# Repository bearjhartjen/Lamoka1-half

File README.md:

<h1 align="center">
  
  <br>
  Lamoka1/2
</h1>

<p align="center">
  PIE v1.9 works on this board.
  For more information on PIE, go
  <a href="SOFTWARE/README.md">here</a>.
</p>

<p align="center">
  <a href="https://htmlpreview.github.io/?https://raw.githubusercontent.com/bearjhartjen/Lamoka1-half/master/HARDWARE/Kicadfiles/Lamoka1-half/BOM/ibom.html">
    <strong>View Interactive BOM</strong>
  </a>
</p>

---

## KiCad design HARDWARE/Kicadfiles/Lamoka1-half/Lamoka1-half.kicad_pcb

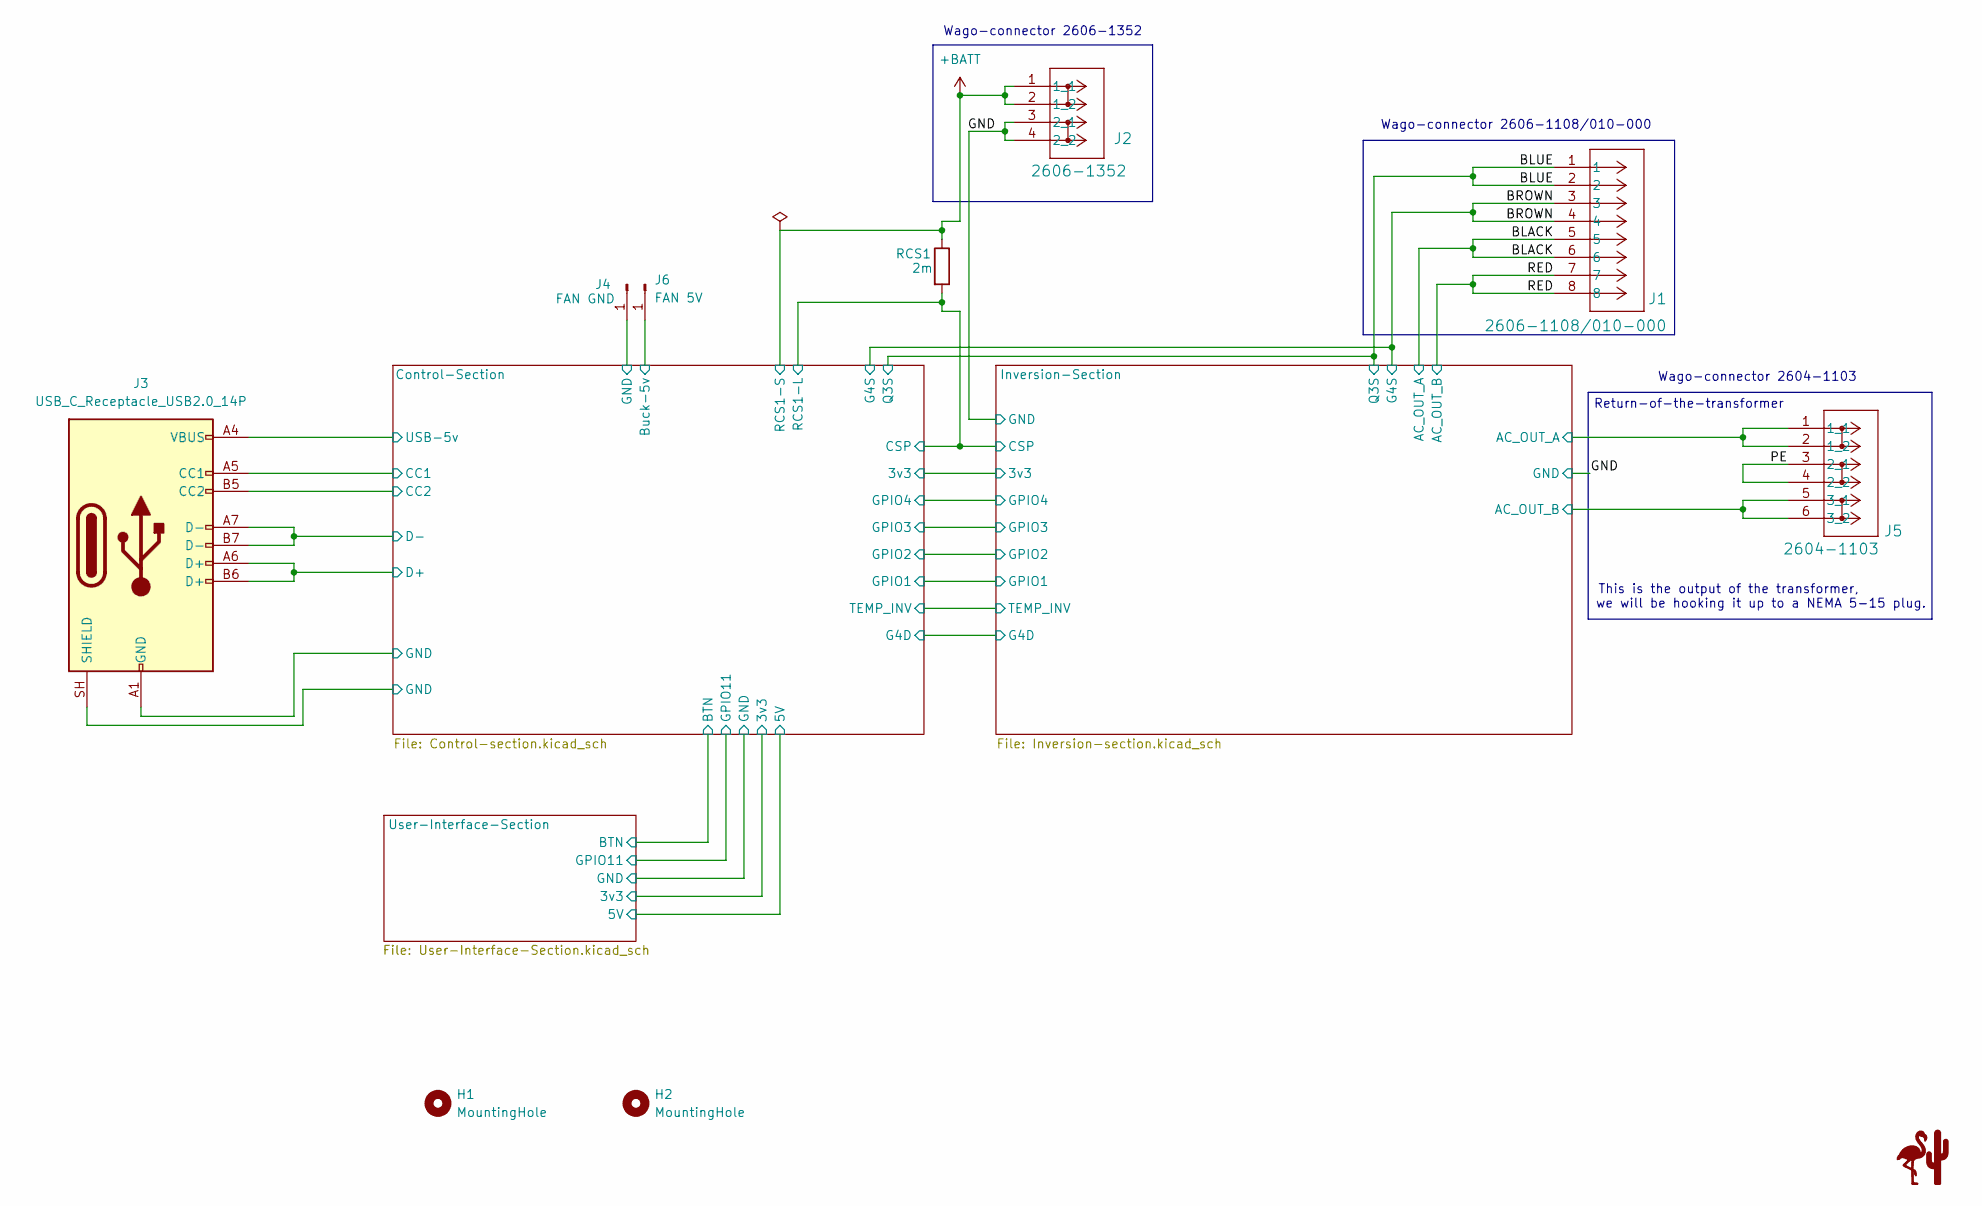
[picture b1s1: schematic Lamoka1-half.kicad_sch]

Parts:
H1, H2: MountingHole; MountingHole_3.2mm_M3
J1: 2606-1108/010-000; CONN8_2606-1108&slash_010-000_WAG; MPN 2606-1108/010-000
J2: 2606-1352; CONN2_2606-1352_WAG; MPN 2606-1352
J3: USB_C_Receptacle_USB2.0_14P; USB_C_Receptacle_HRO_TYPE-C-31-M-12; MPN TYPE-C-31-M-12
J4: FAN GND; SolderWirePad_1x01_SMD_3x6mm
J5: 2604-1103; CONN3_2604-1103_WAG; MPN 2604-1103
J6: FAN 5V; SolderWirePad_1x01_SMD_3x6mm
RCS1: 2m; R_2512_6332Metric; MPN CSNL2512FT2L00

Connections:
+BATT: J2.1 (1_1), J2.2 (1_2), RCS1.1; also elsewhere on the board
/BLACK: J1.5, J1.6, J5.1 (1_1), J5.2 (1_2)
/BLUE: J1.1, J1.2; also elsewhere on the board
/BROWN: J1.3, J1.4; also elsewhere on the board
/Control-Section/Buck-5v: J6.1 (Pin_1_1); also elsewhere on the board
/Control-Section/CC1: J3.A5 (CC1); also elsewhere on the board
/Control-Section/CC2: J3.B5 (CC2); also elsewhere on the board
/Control-Section/D+: J3.A6 (D+), J3.B6 (D+); also elsewhere on the board
/Control-Section/D-: J3.A7 (D-), J3.B7 (D-); also elsewhere on the board
/Control-Section/USB-5v: J3.A4 (VBUS), J3.A9 (VBUS), J3.B4 (VBUS), J3.B9 (VBUS); also elsewhere on the board
/Inversion-Section/CSP: RCS1.2; also elsewhere on the board
/PE: J5.3 (2_1), J5.4 (2_2)
/RED: J1.7, J1.8, J5.5 (3_1), J5.6 (3_2)
GND: J2.3 (2_1), J2.4 (2_2), J3.A1 (GND), J3.A12 (GND), J3.B1 (GND), J3.B12 (GND), J3.SH (SHIELD), J4.1 (Pin_1_1); also elsewhere on the board

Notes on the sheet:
This is the output of the transformer,
Wago-connector 2606-1108/010-000
Wago-connector 2604-1103
Return-of-the-transformer
Wago-connector 2606-1352
we will be hooking it up to a NEMA 5-15 plug.

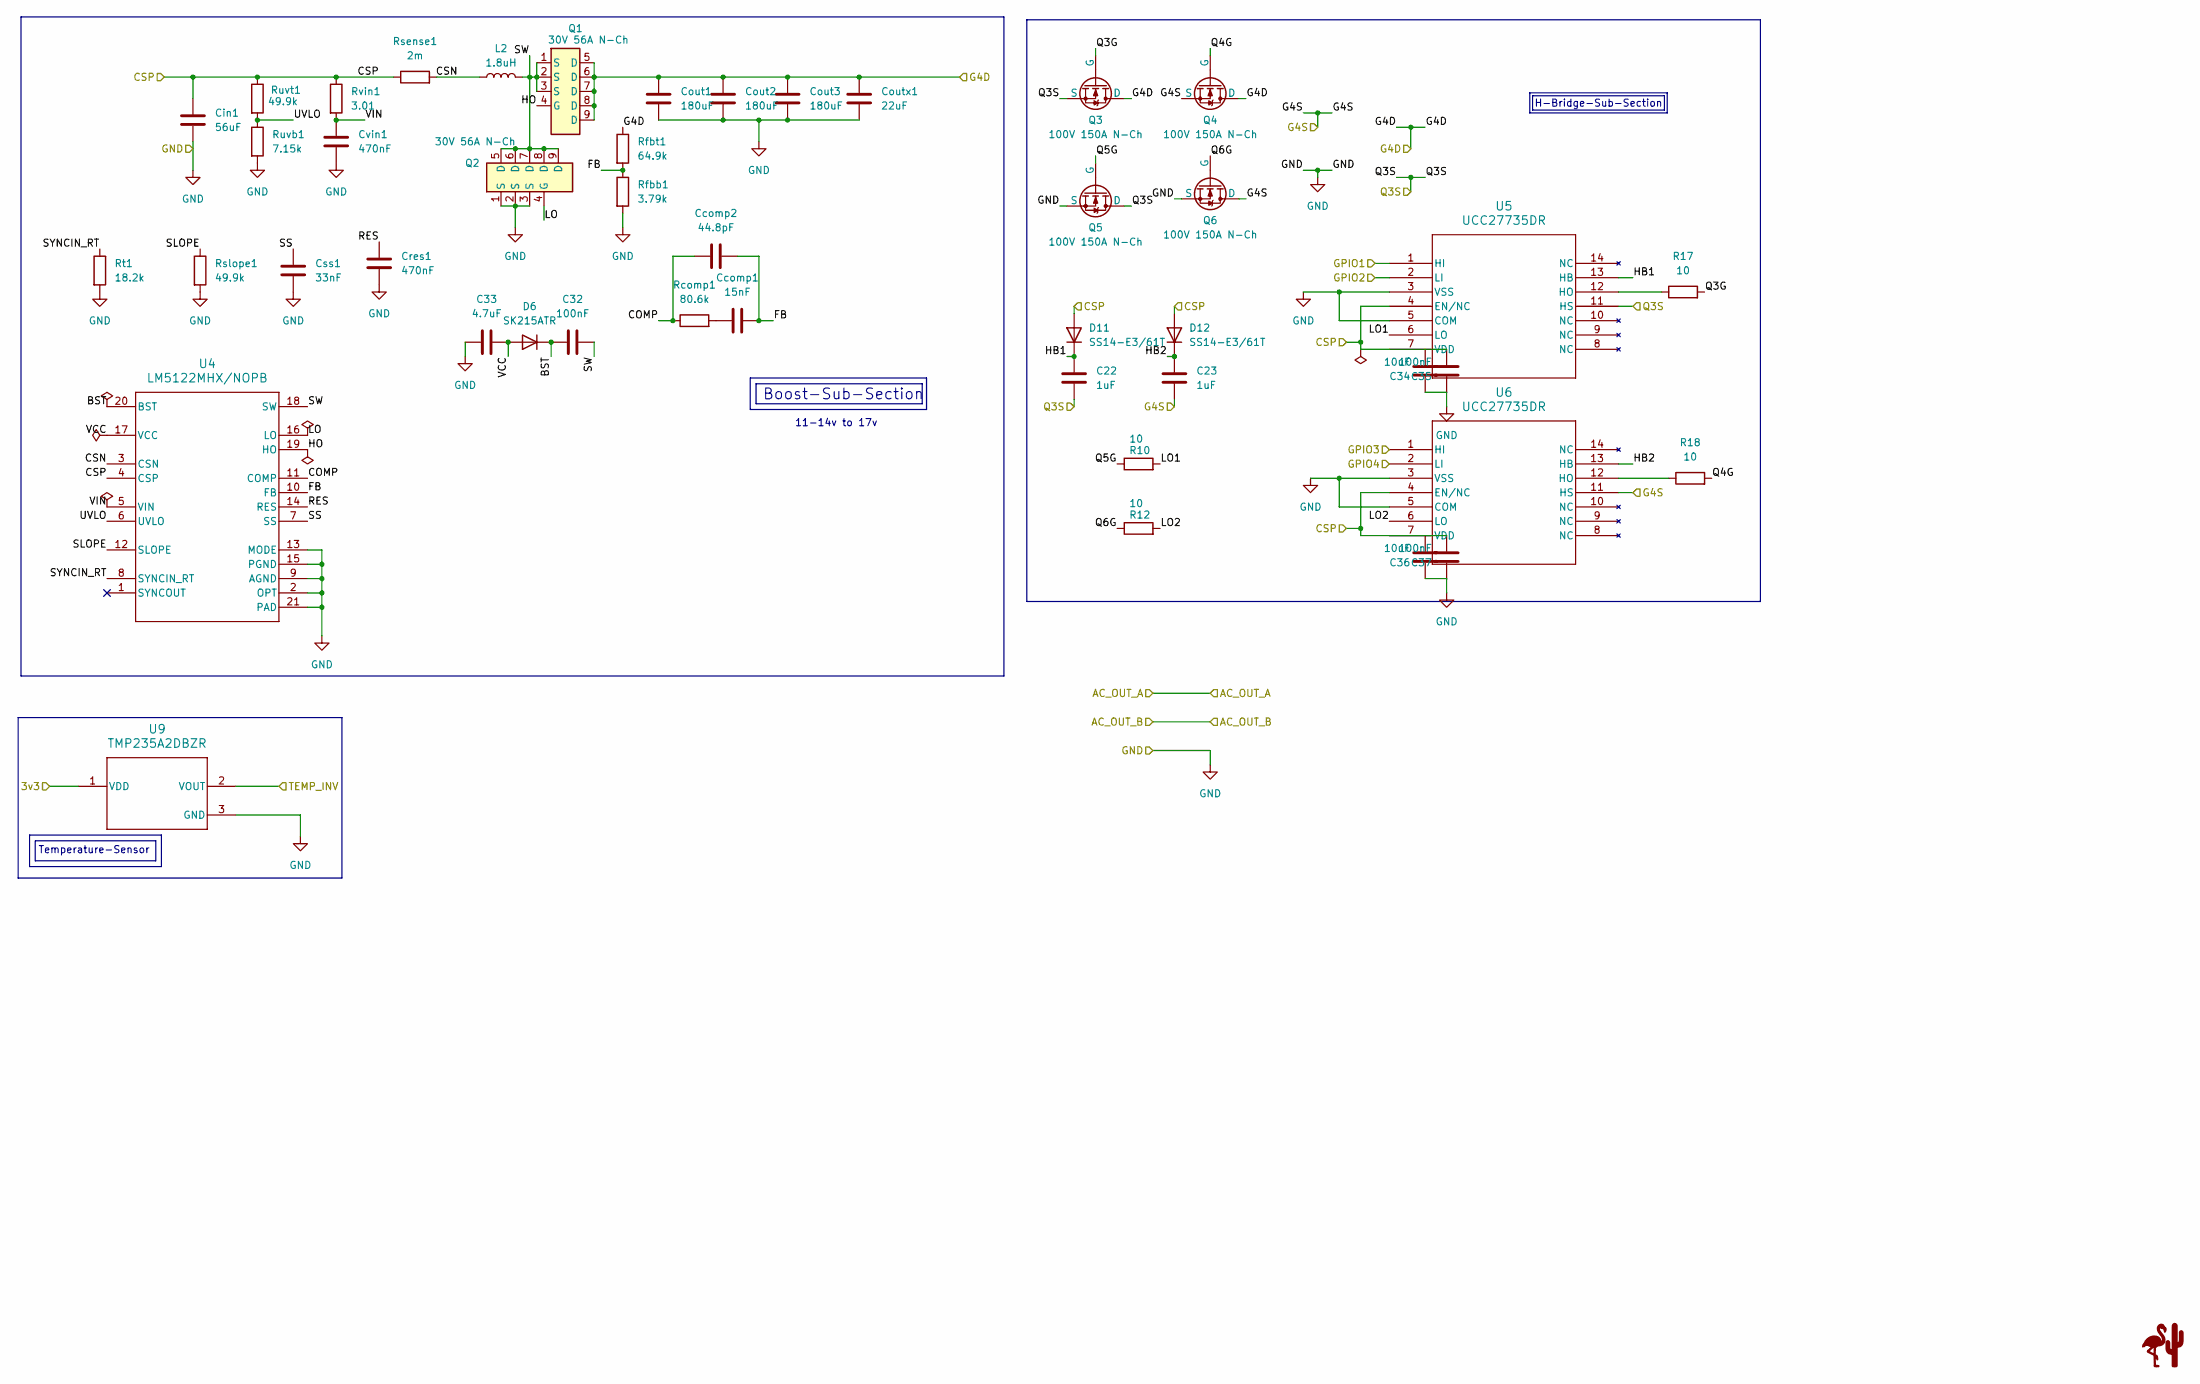
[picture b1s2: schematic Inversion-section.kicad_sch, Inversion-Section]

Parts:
C22, C23: 1uF; C_0805_2012Metric; MPN GRM21BR71H105KA12L
C32: 100nF; C_0805_2012Metric; MPN 08053C104KAT2A
C33: 4.7uF; C_0805_2012Metric; MPN MSAST21GAB5475MTNAO1
C34, C36: 10uF; C_0805_2012Metric; MPN GRM21BZ71E106KE15L
C35, C37: 100nF; C_0603_1608Metric; MPN CL10B104KB8NNNC
Ccomp1: 15nF; C_0805_2012Metric; MPN CGA4F1C0G2A153J085AE
Ccomp2: 44.8pF; C_0402_1005Metric; MPN GRM1555C1H448JA01D
Cin1: 56uF; CP_Elec_5x5.9; MPN 20SVPF56MX
Cout1: 180uF; CP_Elec_8x11.9_Cout1; MPN 35SVPK180M
Cout2: 180uF; CP_Elec_8x11.9_Cout2; MPN 35SVPK180M
Cout3: 180uF; CP_Elec_8x11.9_Cout3; MPN 35SVPK180M
Coutx1: 22uF; C_1206_3216Metric; MPN C3216X5R1V226M160AC
Cres1: 470nF; C_0805_2012Metric; MPN TMK212BJ474KD-T
Css1: 33nF; C_0402_1005Metric; MPN GRM155R71A333KA01D
Cvin1: 470nF; C_0402_1005Metric; MPN C1005X5R1V474K050BC
D6: SK215ATR; D_SMA; MPN SK215ATR
D11, D12: SS14-E3/61T; D_SMA; MPN SS14-E3/61T
L2: 1.8uH; L_Coilcraft_XAL1580-182; MPN XAL1580-182MEB
Q1, Q2: 30V 56A N-Ch; DQG0008A; MPN CSD17304Q3
Q3, Q4, Q5, Q6: 100V 150A N-Ch; TO-220-3_Vertical; MPN CSD19536KCS
R10, R12, R17, R18: 10; R_1206_3216Metric; MPN RC1206FR-0710RL
Rcomp1: 80.6k; R_0201_0603Metric; MPN RC0201FR-0780K6L
Rfbb1: 3.79k; R_0402_1005Metric; MPN CRCW04023K79FKED
Rfbt1: 64.9k; R_0402_1005Metric; MPN CRCW040264K9FKED
Rsense1: 2m; R_2512_6332Metric; MPN CSNL2512FT2L00
Rslope1: 49.9k; R_0201_0603Metric; MPN RC0201FR-0749K9L
Rt1: 18.2k; R_0402_1005Metric; MPN CRCW040218K2FKED
Ruvb1: 7.15k; R_0402_1005Metric; MPN CRCW04027K15FKED
Ruvt1: 49.9k; R_0402_1005Metric; MPN CRCW040249K9FKED
Rvin1: 3.01; R_0402_1005Metric; MPN CRCW04023R01FKED
U4: LM5122MHX/NOPB; PWP0020A_N; MPN LM5122MHX/NOPB
U5, U6: UCC27735DR; SOIC_14L_TEX; MPN UCC27735DR
U9: TMP235A2DBZR; DBZ0003A-IPC_A; MPN TMP235A2DBZR

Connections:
/BLUE: C22.2, Q3.3 (S), Q5.2 (D), U5.11 (HS); also elsewhere on the board
/BROWN: C23.2, Q4.3 (S), Q6.2 (D), U6.11 (HS); also elsewhere on the board
/Control-Section/3v3: U9.1 (VDD); also elsewhere on the board
/Control-Section/GPIO1: U5.1 (HI); also elsewhere on the board
/Control-Section/GPIO2: U5.2 (LI); also elsewhere on the board
/Control-Section/GPIO3: U6.1 (HI); also elsewhere on the board
/Control-Section/GPIO4: U6.2 (LI); also elsewhere on the board
/Control-Section/TEMP_INV: U9.2 (VOUT); also elsewhere on the board
/Inversion-Section/BST: C32.1, D6.1 (K), U4.20 (BST)
/Inversion-Section/COMP: Ccomp2.1, Rcomp1.1, U4.11 (COMP)
/Inversion-Section/CSN: L2.1, Rsense1.2, U4.3 (CSN)
/Inversion-Section/CSP: C34.2, C35.2, C36.2, C37.2, Cin1.1, D11.2 (A), D12.2 (A), Rsense1.1, Ruvt1.1, Rvin1.1, U4.4 (CSP), U5.4 (EN/NC), U5.7 (VDD), U6.4 (EN/NC), U6.7 (VDD); also elsewhere on the board
/Inversion-Section/FB: Ccomp1.2, Ccomp2.2, Rfbb1.1, Rfbt1.2, U4.10 (FB)
/Inversion-Section/G4D: Cout1.1, Cout2.1, Cout3.1, Coutx1.1, Q1.5 (D), Q1.6 (D), Q1.7 (D), Q1.8 (D), Q1.9 (D), Q3.2 (D), Q4.2 (D), Rfbt1.1; also elsewhere on the board
/Inversion-Section/HB1: C22.1, D11.1 (K), U5.13 (HB)
/Inversion-Section/HB2: C23.1, D12.1 (K), U6.13 (HB)
/Inversion-Section/HO: Q1.4 (G), U4.19 (HO)
/Inversion-Section/LO: Q2.4 (G), U4.16 (LO)
/Inversion-Section/LO1: R10.2, U5.6 (LO)
/Inversion-Section/LO2: R12.2, U6.6 (LO)
/Inversion-Section/Q3G: Q3.1 (G), R17.2
/Inversion-Section/Q4G: Q4.1 (G), R18.2
/Inversion-Section/Q5G: Q5.1 (G), R10.1
/Inversion-Section/Q6G: Q6.1 (G), R12.1
/Inversion-Section/RES: Cres1.1, U4.14 (RES)
/Inversion-Section/SLOPE: Rslope1.1, U4.12 (SLOPE)
/Inversion-Section/SS: Css1.1, U4.7 (SS)
/Inversion-Section/SW: C32.2, L2.2, Q1.1 (S), Q1.2 (S), Q1.3 (S), Q2.5 (D), Q2.6 (D), Q2.7 (D), Q2.8 (D), Q2.9 (D), U4.18 (SW)
/Inversion-Section/SYNCIN_RT: Rt1.1, U4.8 (SYNCIN_RT)
/Inversion-Section/UVLO: Ruvb1.1, Ruvt1.2, U4.6 (UVLO)
/Inversion-Section/VCC: C33.2, D6.2 (A), U4.17 (VCC)
/Inversion-Section/VIN: Cvin1.1, Rvin1.2, U4.5 (VIN)
GND: C33.1, C34.1, C35.1, C36.1, C37.1, Cin1.2, Cout1.2, Cout2.2, Cout3.2, Coutx1.2, Cres1.2, Css1.2, Cvin1.2, Q2.1 (S), Q2.2 (S), Q2.3 (S), Q5.3 (S), Q6.3 (S), Rfbb1.2, Rslope1.2, Rt1.2, Ruvb1.2, U4.2 (OPT), U4.9 (AGND), U4.13 (MODE), U4.15 (PGND), U4.21 (PAD), U4.V, U5.3 (VSS), U5.5 (COM), U6.3 (VSS), U6.5 (COM), U9.3 (GND); also elsewhere on the board
unnamed: Ccomp1.1, Rcomp1.2
unnamed: R17.1, U5.12 (HO)
unnamed: R18.1, U6.12 (HO)

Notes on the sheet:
11-14v to 17v
H-Bridge-Sub-Section
Boost-Sub-Section
Temperature-Sensor

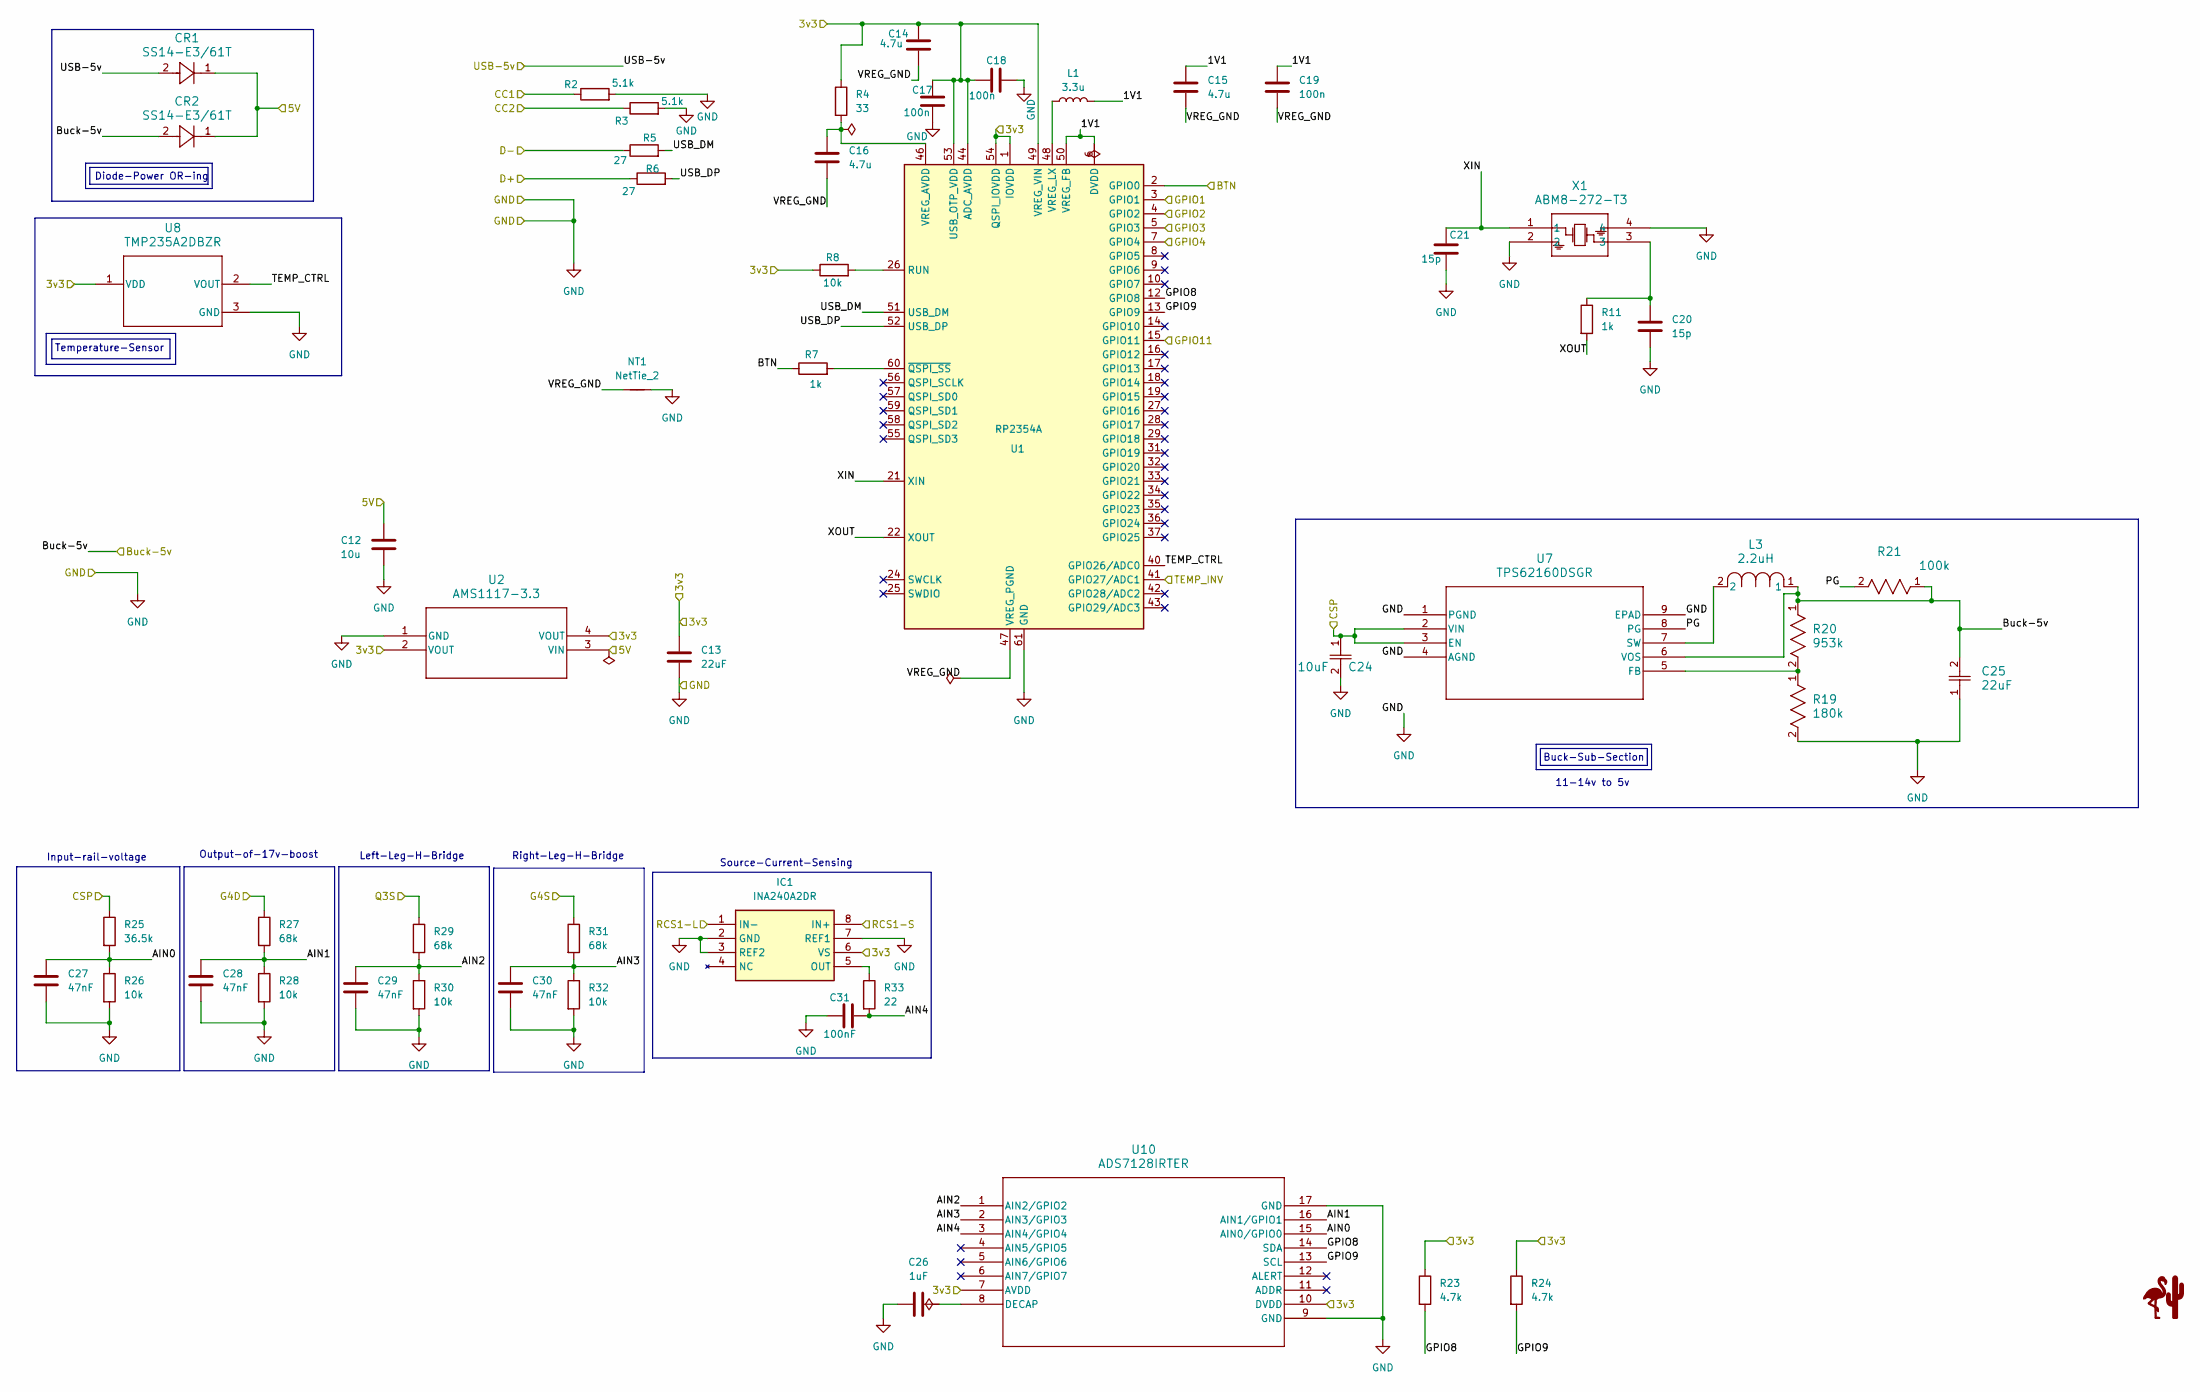
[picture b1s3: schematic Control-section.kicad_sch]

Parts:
C12: 10u; C_0402_1005Metric; MPN CL05A106MQ5NUNC
C13: 22uF; CP_EIA-3216-18_Kemet-A; MPN T491A226K010AT
C14, C15, C16: 4.7u; C_0603_1608Metric; MPN CL10A475KP8NNNC
C17, C18, C19: 100n; C_0402_1005Metric; MPN CL05B104KO5NNNC
C20, C21: 15p; C_0402_1005Metric; MPN 0402CG150J500NT
C24: 10uF; CAPC2114X145N; MPN TMK212BBJ106KG-T
C25: 22uF; G-31_MUR; MPN GRM31CR71A226KE15L
C26: 1uF; C_0603_1608Metric; MPN CL10A105KA8NNNC
C27, C28, C29, C30: 47nF; C_0603_1608Metric; MPN CL10B473KB8NNNC
C31: 100nF; C_0603_1608Metric; MPN CL10B104KB8NNNC
CR1, CR2: SS14-E3/61T; DO-214AC_VIS; MPN SS14-E3/61T
IC1: INA240A2DR; SOIC127P600X175-8N; MPN INA240A2DR; Mouser Part Number 595-INA240A2DR
L1: 3.3u; AOTAB201610S3R3101T; MPN AOTA-B201610S3R3-101-T
L3: 2.2uH; IND_PA4332.222NLT_PUL; MPN PA4332.222NLT
NT1: NetTie_2; NetTie-2_SMD_Pad0.5mm
R2, R3: 5.1k; RC0603N_YAG; MPN RC0603FR-075K1L
R4: 33; R_0603_1608Metric; MPN RC0603FR-0733RL
R5, R6: 27; R_0603_1608Metric; MPN RC0603FR-0727RL
R7, R11: 1k; R_0402_1005Metric; MPN RC0402FR-071KL
R8, R26, R28, R30, R32: 10k; R_0603_1608Metric; MPN RC0603FR-0710KL
R19: 180k; RC0603N_YAG; MPN RC0603FR-07180KL
R20: 953k; RC0402N_VIS; MPN CRCW0402953KFKED
R21: 100k; RES_CRCW_0402_VIS; MPN CRCW0402100KFKED
R23, R24: 4.7k; R_0603_1608Metric; MPN RC0603FR-074K7L
R25: 36.5k; R_0603_1608Metric; MPN RC0603FR-0736K5L
R27, R29, R31: 68k; R_0603_1608Metric; MPN RC0603FR-0768KL
R33: 22; R_0603_1608Metric; MPN RC0603FR-0722RL
U1: RP2354A; QFN-60-1EP_7x7mm_P0.4mm_EP3.4x3.4mm; MPN RP2354A
U2: AMS1117-3.3; SOT-223-3_TabPin2; MPN AMS1117-3.3
U7: TPS62160DSGR; DSG8_1P6X0P9; MPN TPS62160DSGR
U8: TMP235A2DBZR; DBZ0003A-IPC_A; MPN TMP235A2DBZR
U10: ADS7128IRTER; WQFN16_RTE_TEX; MPN ADS7128IRTER
X1: ABM8-272-T3; ABM8272T3; MPN ABM8-272-T3

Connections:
+BATT: IC1.8 (IN+); also elsewhere on the board
/BLUE: R29.1; also elsewhere on the board
/BROWN: R31.1; also elsewhere on the board
/Control-Section/1V1: C15.1, C19.1, L1.2, U1.6 (DVDD), U1.23 (DVDD), U1.39 (DVDD), U1.50 (VREG_FB)
/Control-Section/3v3: C13.1, C14.1, C17.1, C18.1, IC1.6 (VS), R4.1, R8.1, R23.1, R24.1, U1.1 (IOVDD), U1.11 (IOVDD), U1.20 (IOVDD), U1.30 (IOVDD), U1.38 (IOVDD), U1.44 (ADC_AVDD), U1.45 (IOVDD), U1.49 (VREG_VIN), U1.53 (USB_OTP_VDD), U1.54 (QSPI_IOVDD), U2.2 (VOUT), U2.4 (VOUT), U8.1 (VDD), U10.7 (AVDD), U10.10 (DVDD); also elsewhere on the board
/Control-Section/5V: C12.2, CR1.1, CR2.1, U2.3 (VIN); also elsewhere on the board
/Control-Section/AIN0: C27.1, R25.2, R26.1, U10.15 (AIN0/GPIO0)
/Control-Section/AIN1: C28.1, R27.2, R28.1, U10.16 (AIN1/GPIO1)
/Control-Section/AIN2: C29.1, R29.2, R30.1, U10.1 (AIN2/GPIO2)
/Control-Section/AIN3: C30.1, R31.2, R32.1, U10.2 (AIN3/GPIO3)
/Control-Section/AIN4: C31.1, R33.2, U10.3 (AIN4/GPIO4)
/Control-Section/BTN: R7.1, U1.2 (GPIO0); also elsewhere on the board
/Control-Section/Buck-5v: C25.2, CR2.2, L3.1, R20.1, R21.1, U7.6 (VOS); also elsewhere on the board
/Control-Section/CC1: R2.1; also elsewhere on the board
/Control-Section/CC2: R3.1; also elsewhere on the board
/Control-Section/D+: R6.1; also elsewhere on the board
/Control-Section/D-: R5.1; also elsewhere on the board
/Control-Section/GPIO1: U1.3 (GPIO1); also elsewhere on the board
/Control-Section/GPIO2: U1.4 (GPIO2); also elsewhere on the board
/Control-Section/GPIO3: U1.5 (GPIO3); also elsewhere on the board
/Control-Section/GPIO4: U1.7 (GPIO4); also elsewhere on the board
/Control-Section/GPIO8: R23.2, U1.12 (GPIO8), U10.14 (SDA)
/Control-Section/GPIO9: R24.2, U1.13 (GPIO9), U10.13 (SCL)
/Control-Section/GPIO11: U1.15 (GPIO11); also elsewhere on the board
/Control-Section/PG: R21.2, U7.8 (PG)
/Control-Section/TEMP_CTRL: U1.40 (GPIO26/ADC0), U8.2 (VOUT)
/Control-Section/TEMP_INV: U1.41 (GPIO27/ADC1); also elsewhere on the board
/Control-Section/USB-5v: CR1.2; also elsewhere on the board
/Control-Section/USB_DM: R5.2, U1.51 (USB_DM)
/Control-Section/USB_DP: R6.2, U1.52 (USB_DP)
/Control-Section/VREG_GND: C14.2, C15.2, C16.2, C19.2, NT1.1, U1.47 (VREG_PGND)
/Control-Section/XIN: C21.1, U1.21 (XIN), X1.1
/Control-Section/XOUT: R11.2, U1.22 (XOUT)
/Inversion-Section/CSP: C24.1, IC1.1 (IN-), R25.1, U7.2 (VIN), U7.3 (EN); also elsewhere on the board
/Inversion-Section/G4D: R27.1; also elsewhere on the board
GND: C12.1, C13.2, C17.2, C18.2, C20.2, C21.2, C24.2, C25.1, C26.2, C27.2, C28.2, C29.2, C30.2, C31.2, IC1.2 (GND), IC1.3 (REF2), IC1.7 (REF1), NT1.2, R2.2, R3.2, R19.2, R26.2, R28.2, R30.2, R32.2, U1.61 (GND), U2.1 (GND), U7.1 (PGND), U7.4 (AGND), U7.9 (EPAD), U8.3 (GND), U10.9 (GND), U10.17 (GND), X1.2, X1.4; also elsewhere on the board
unnamed: C20.1, R11.1, X1.3
unnamed: IC1.5 (OUT), R33.1
unnamed: R8.2, U1.26 (RUN)
unnamed: C16.1, R4.2, U1.46 (VREG_AVDD)
unnamed: L1.1, U1.48 (VREG_LX)
unnamed: R7.2, U1.60 (~QSPI_SS)
unnamed: R19.1, R20.2, U7.5 (FB)
unnamed: L3.2, U7.7 (SW)
unnamed: C26.1, U10.8 (DECAP)

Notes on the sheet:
Left-Leg-H-Bridge
Source-Current-Sensing
Input-rail-voltage
11-14v to 5v
Right-Leg-H-Bridge
Output-of-17v-boost
Temperature-Sensor
Diode-Power OR-ing
Buck-Sub-Section

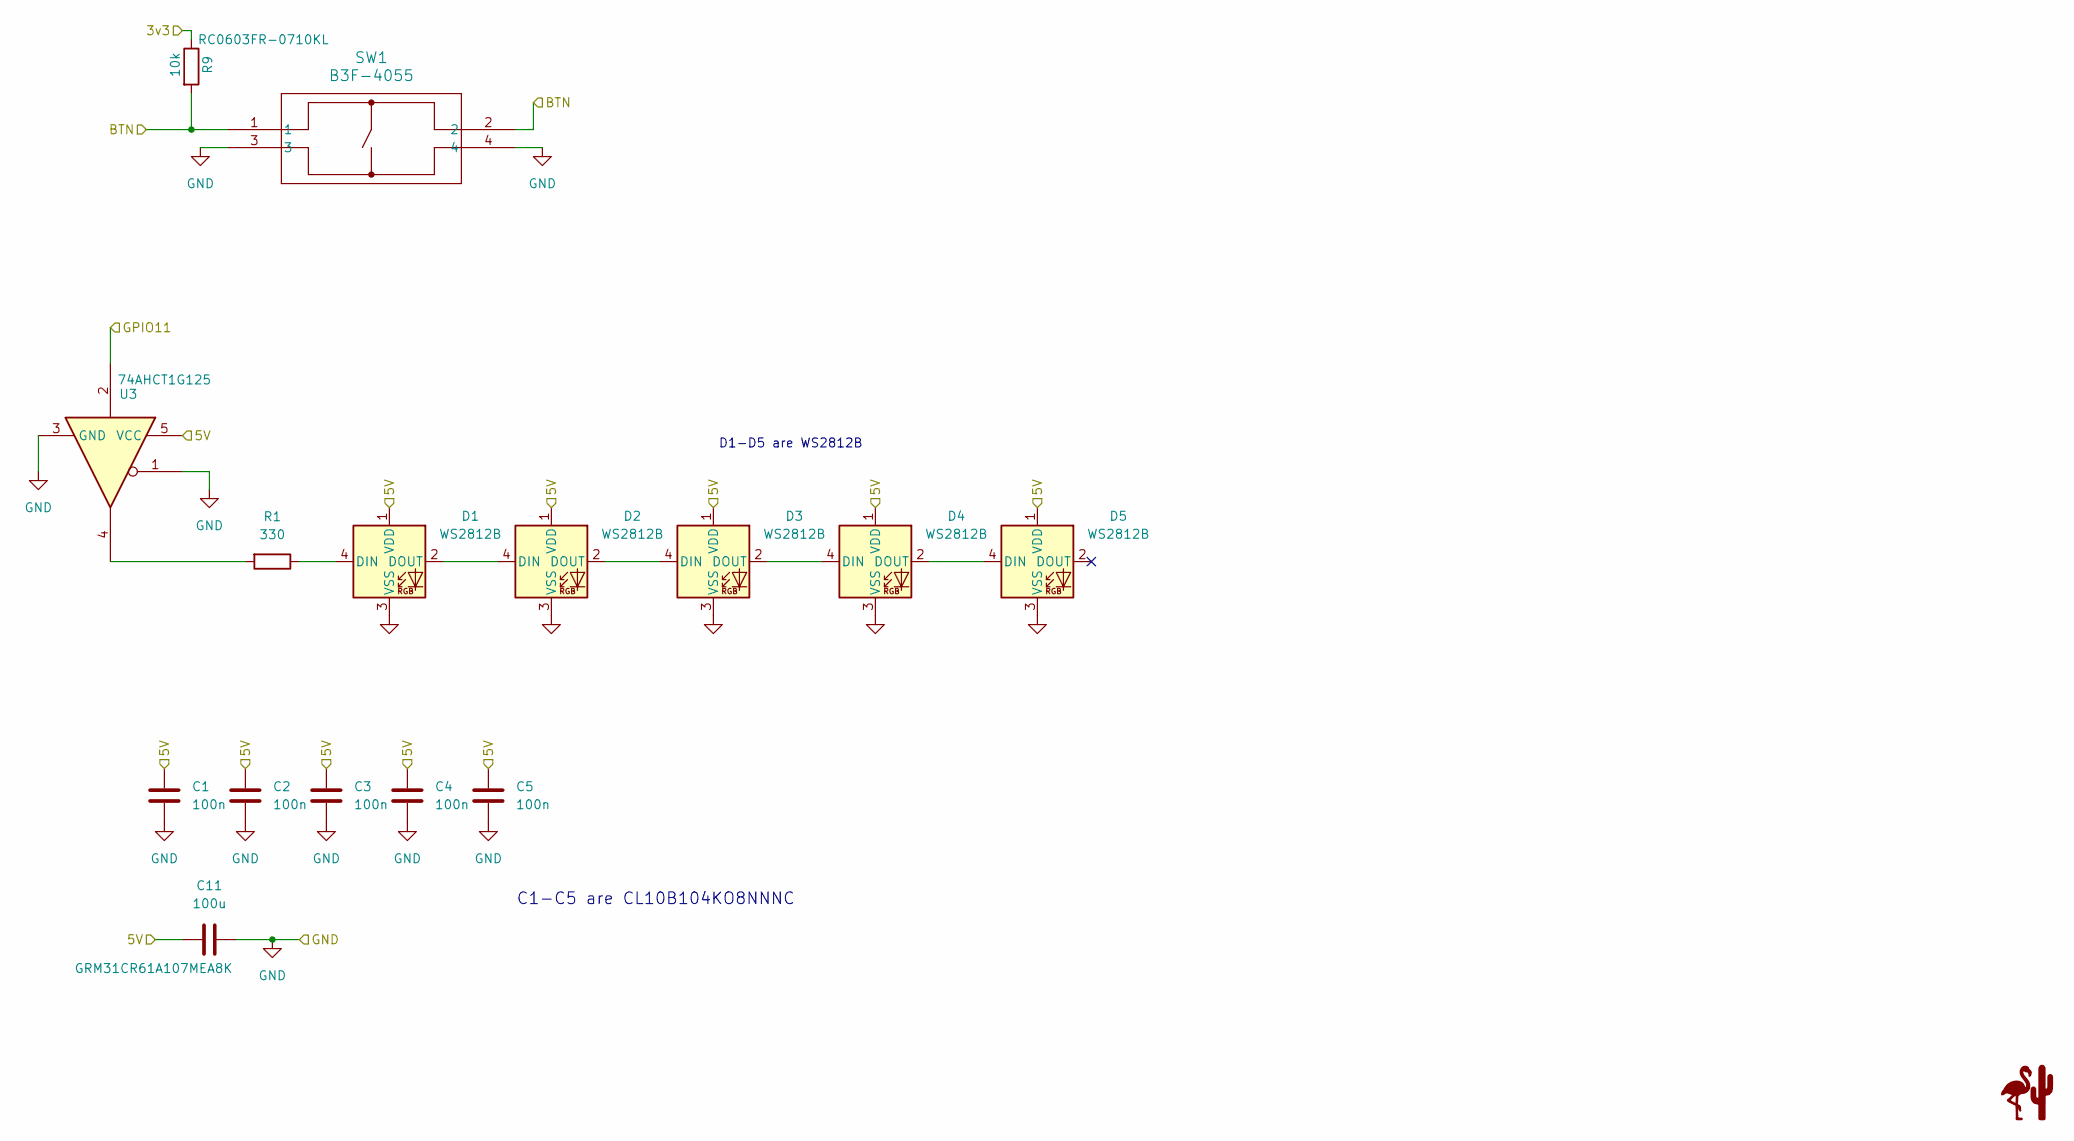
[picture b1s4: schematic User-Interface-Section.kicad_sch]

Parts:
C1, C2, C3, C4, C5: 100n; C_0603_1608Metric; MPN CL10B104KO8NNNC
C11: 100u; C_1206_3216Metric; MPN GRM31CR61A107MEA8K
D1, D2, D3, D4, D5: WS2812B; LED_WS2812B_PLCC4_5.0x5.0mm_P3.2mm; MPN WS2812B
R1: 330; R_0603_1608Metric; MPN RC0603FR-07330RL
R9: 10k; R_0603_1608Metric; MPN RC0603FR-0710KL
SW1: B3F-4055; SW_B3F-4050_OMR; MPN B3F-4055
U3: 74AHCT1G125; SOT-23-5; MPN SN74AHCT1G125DBVR

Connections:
/Control-Section/3v3: R9.1; also elsewhere on the board
/Control-Section/5V: C1.1, C2.1, C3.1, C4.1, C5.1, C11.1, D1.1 (VDD), D2.1 (VDD), D3.1 (VDD), D4.1 (VDD), D5.1 (VDD), U3.5 (VCC); also elsewhere on the board
/Control-Section/BTN: R9.2, SW1.1, SW1.2; also elsewhere on the board
/Control-Section/GPIO11: U3.2; also elsewhere on the board
GND: C1.2, C2.2, C3.2, C4.2, C5.2, C11.2, D1.3 (VSS), D2.3 (VSS), D3.3 (VSS), D4.3 (VSS), D5.3 (VSS), SW1.3, SW1.4, U3.1, U3.3 (GND); also elsewhere on the board
unnamed: D1.4 (DIN), R1.1
unnamed: D1.2 (DOUT), D2.4 (DIN)
unnamed: D2.2 (DOUT), D3.4 (DIN)
unnamed: D3.2 (DOUT), D4.4 (DIN)
unnamed: D4.2 (DOUT), D5.4 (DIN)
unnamed: R1.2, U3.4

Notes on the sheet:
D1-D5 are WS2812B
C1-C5 are CL10B104KO8NNNC

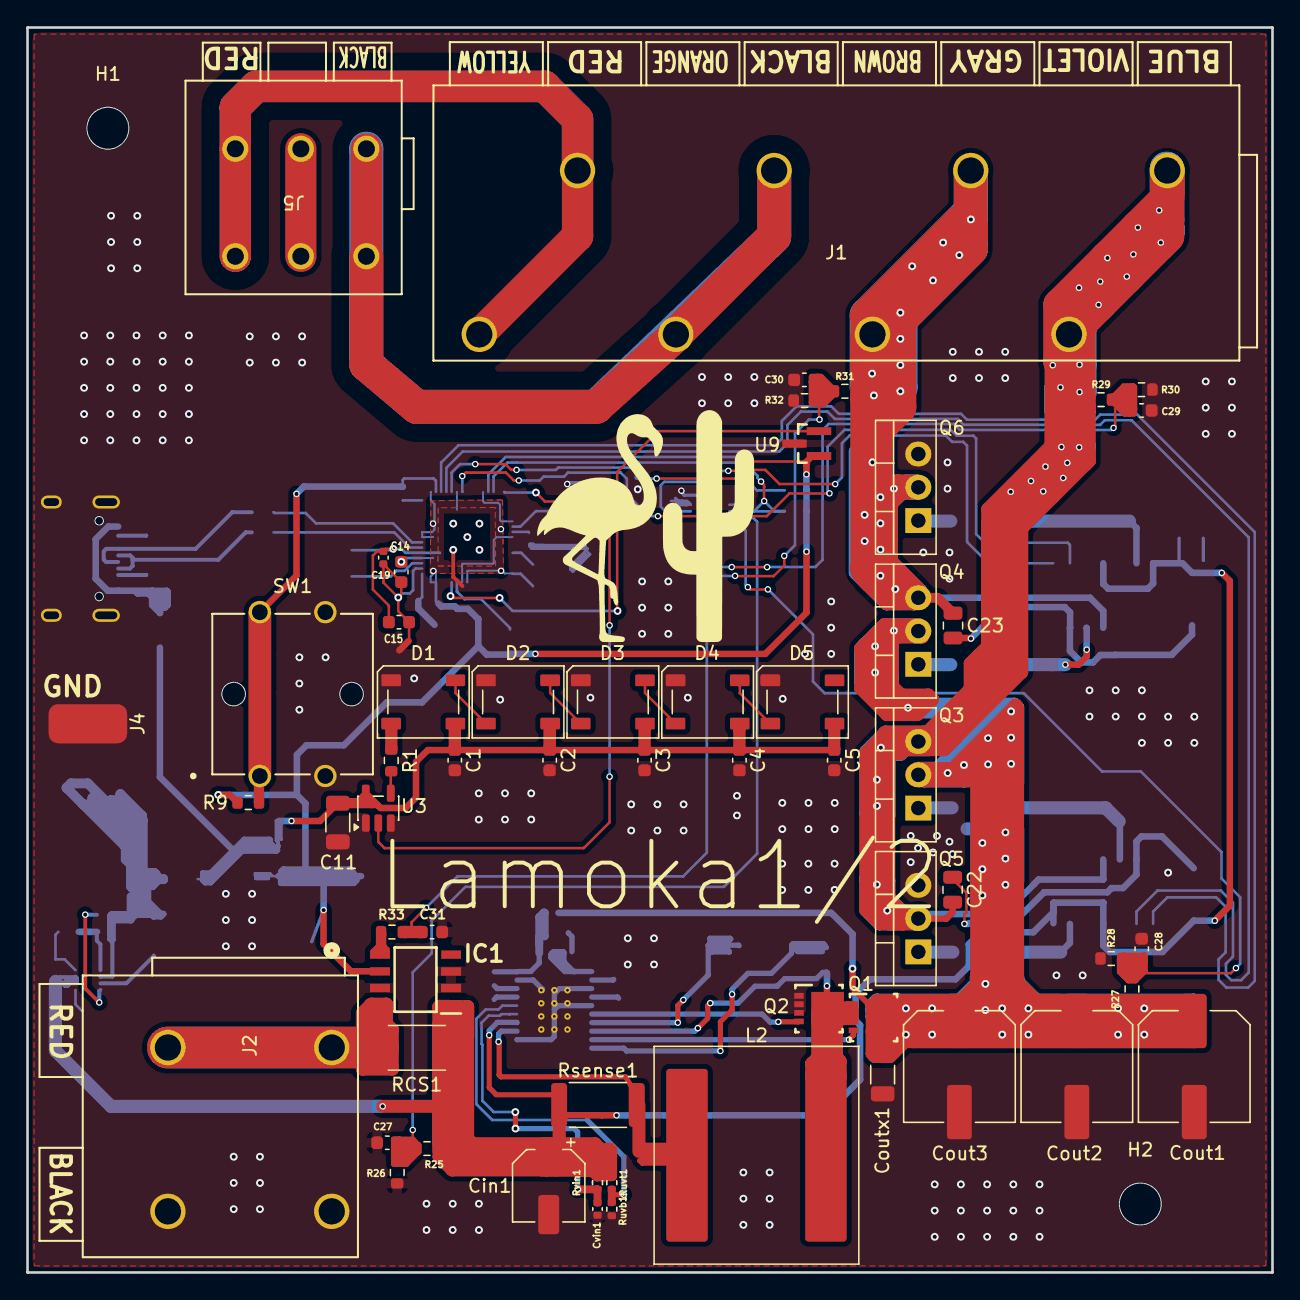
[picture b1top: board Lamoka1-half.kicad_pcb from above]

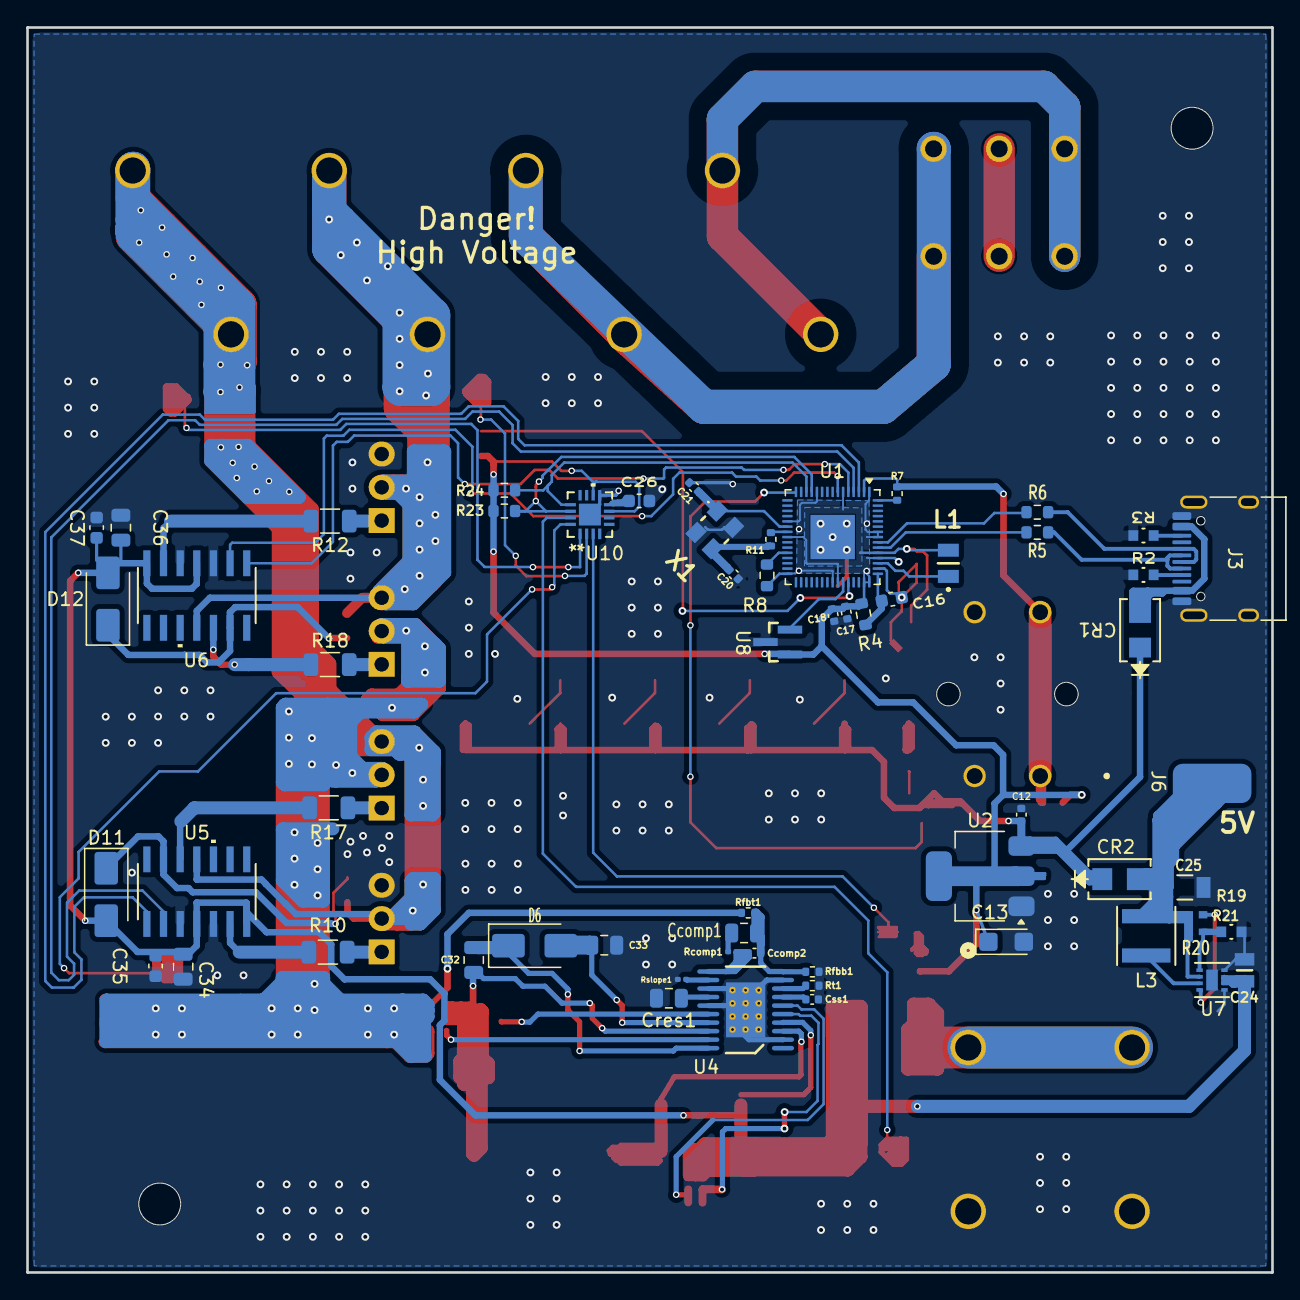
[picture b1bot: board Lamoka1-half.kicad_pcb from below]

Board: 2 copper layers, 95.0 x 95.0 mm, 121 parts (60 on the bottom side), 79 nets.

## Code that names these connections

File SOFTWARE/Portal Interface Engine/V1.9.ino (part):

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#define NUM_LEDS          5
#define BUTTON_PIN        0

#define TEMP_CTRL         26   // TMP235, control-section temperature
#define TEMP_INV          27   // TMP235, inversion-section temperature

#define DEFAULT_BRIGHTNESS 6
#define DEFAULT_SPEED      100
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 *  The H-bridge on the main Lamoka1/2 board has never been energised.
 *  The dead-time between high-side and low-side transitions is created
 *  entirely by this firmware; there is no hardware dead-time generator.
 *  Before the bridge is first enabled with bus power, verify GPIO1–4 on
 *  a scope with the gate-driver inputs exposed: confirm that both inputs
 *  of each half-bridge never go high simultaneously and that the low-side
 *  pulse width is reduced by the dead-time gap on both edges.
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 *
 *  PWM dead-time scheme (from brief, kept in comments)
 *  ---------------------------------------------------
 *  GPIO1 (leg A high) → PWM slice 0 channel B, non-inverted, CC = dA*T
 *  GPIO2 (leg A low)  → PWM slice 1 channel A, inverted,    CC = dA*T + 2*dt
 *  GPIO3 (leg B high) → PWM slice 1 channel B, non-inverted, CC = dB*T
 *  GPIO4 (leg B low)  → PWM slice 2 channel A, inverted,    CC = dB*T + 2*dt
 *
 *  All three slices share TOP = T-1, divider = 1 (150 MHz PWM clock),
 *  up-counting mode.  Before enabling, counters are phased so the low-side
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 *  1.16 times the fundamental in RMS at the design point (16.8 V total
 *  against 14.5 V fundamental at m = 0.941).  A later board
 *  that puts each leg on its own slice
 *  (leg A on slice 1 = GPIO2/GPIO3, leg B on slice 2 = GPIO4/GPIO5, with
 *  the slices 180 degrees apart) would give a true bipolar drive; that is
 *  a pin-assignment change, not a firmware change.
 * ================================================================ */
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// at rated load.  (The A1 20 V/V / 0.04 V/A assumption present in earlier
// V1.9 drafts is incorrect for the fitted part and would report 2.5×
// the true current.)
#define INA240_V_PER_A     0.100f                       // AIN4, 0.100 V/A (INA240A2DR, 50 V/V on RCS1's 2 mΩ)

// AIN2/AIN3 filter (recorded, not corrected).
//
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
static float readTempAdc(uint8_t adcInput) {
  // The TMP235 is an ANALOGUE sensor on this board: the netlist has its
  // VOUT pin (not an I2C device) on GPIO26/ADC0 and GPIO27/ADC1.  Its
  // transfer function is 10 mV/degC with 500 mV at 0 degC, so the reading
  // below is the datasheet's own equation.
  //
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    pwm_init(s, &cfg, false);
  }

  pwm_set_output_polarity(PWM_SLICE_A_LO, true, false);   // GPIO2 inverted
  pwm_set_output_polarity(PWM_SLICE_B_LO, true, false);   // GPIO4 inverted

  // The brief writes "phase of -k*dt" with counters T-dt and T-2dt, but that
  // gives a delayed low-side slice and creates shoot-through at the period
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
  // RP2350 ADC for TMP235 temperature sensors.
  adc_init();
  adc_gpio_init(TEMP_CTRL);
  adc_gpio_init(TEMP_INV);

  // Hardware watchdog.  Safe because the UCC27735 inputs have internal
  // pull-downs that bring the gates low while the MCU is in reset.  The
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

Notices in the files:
HARDWARE/Kicadfiles/Lamoka1-half/Control-section.kicad_sch:
License: CERN-OHL-W-2.0
